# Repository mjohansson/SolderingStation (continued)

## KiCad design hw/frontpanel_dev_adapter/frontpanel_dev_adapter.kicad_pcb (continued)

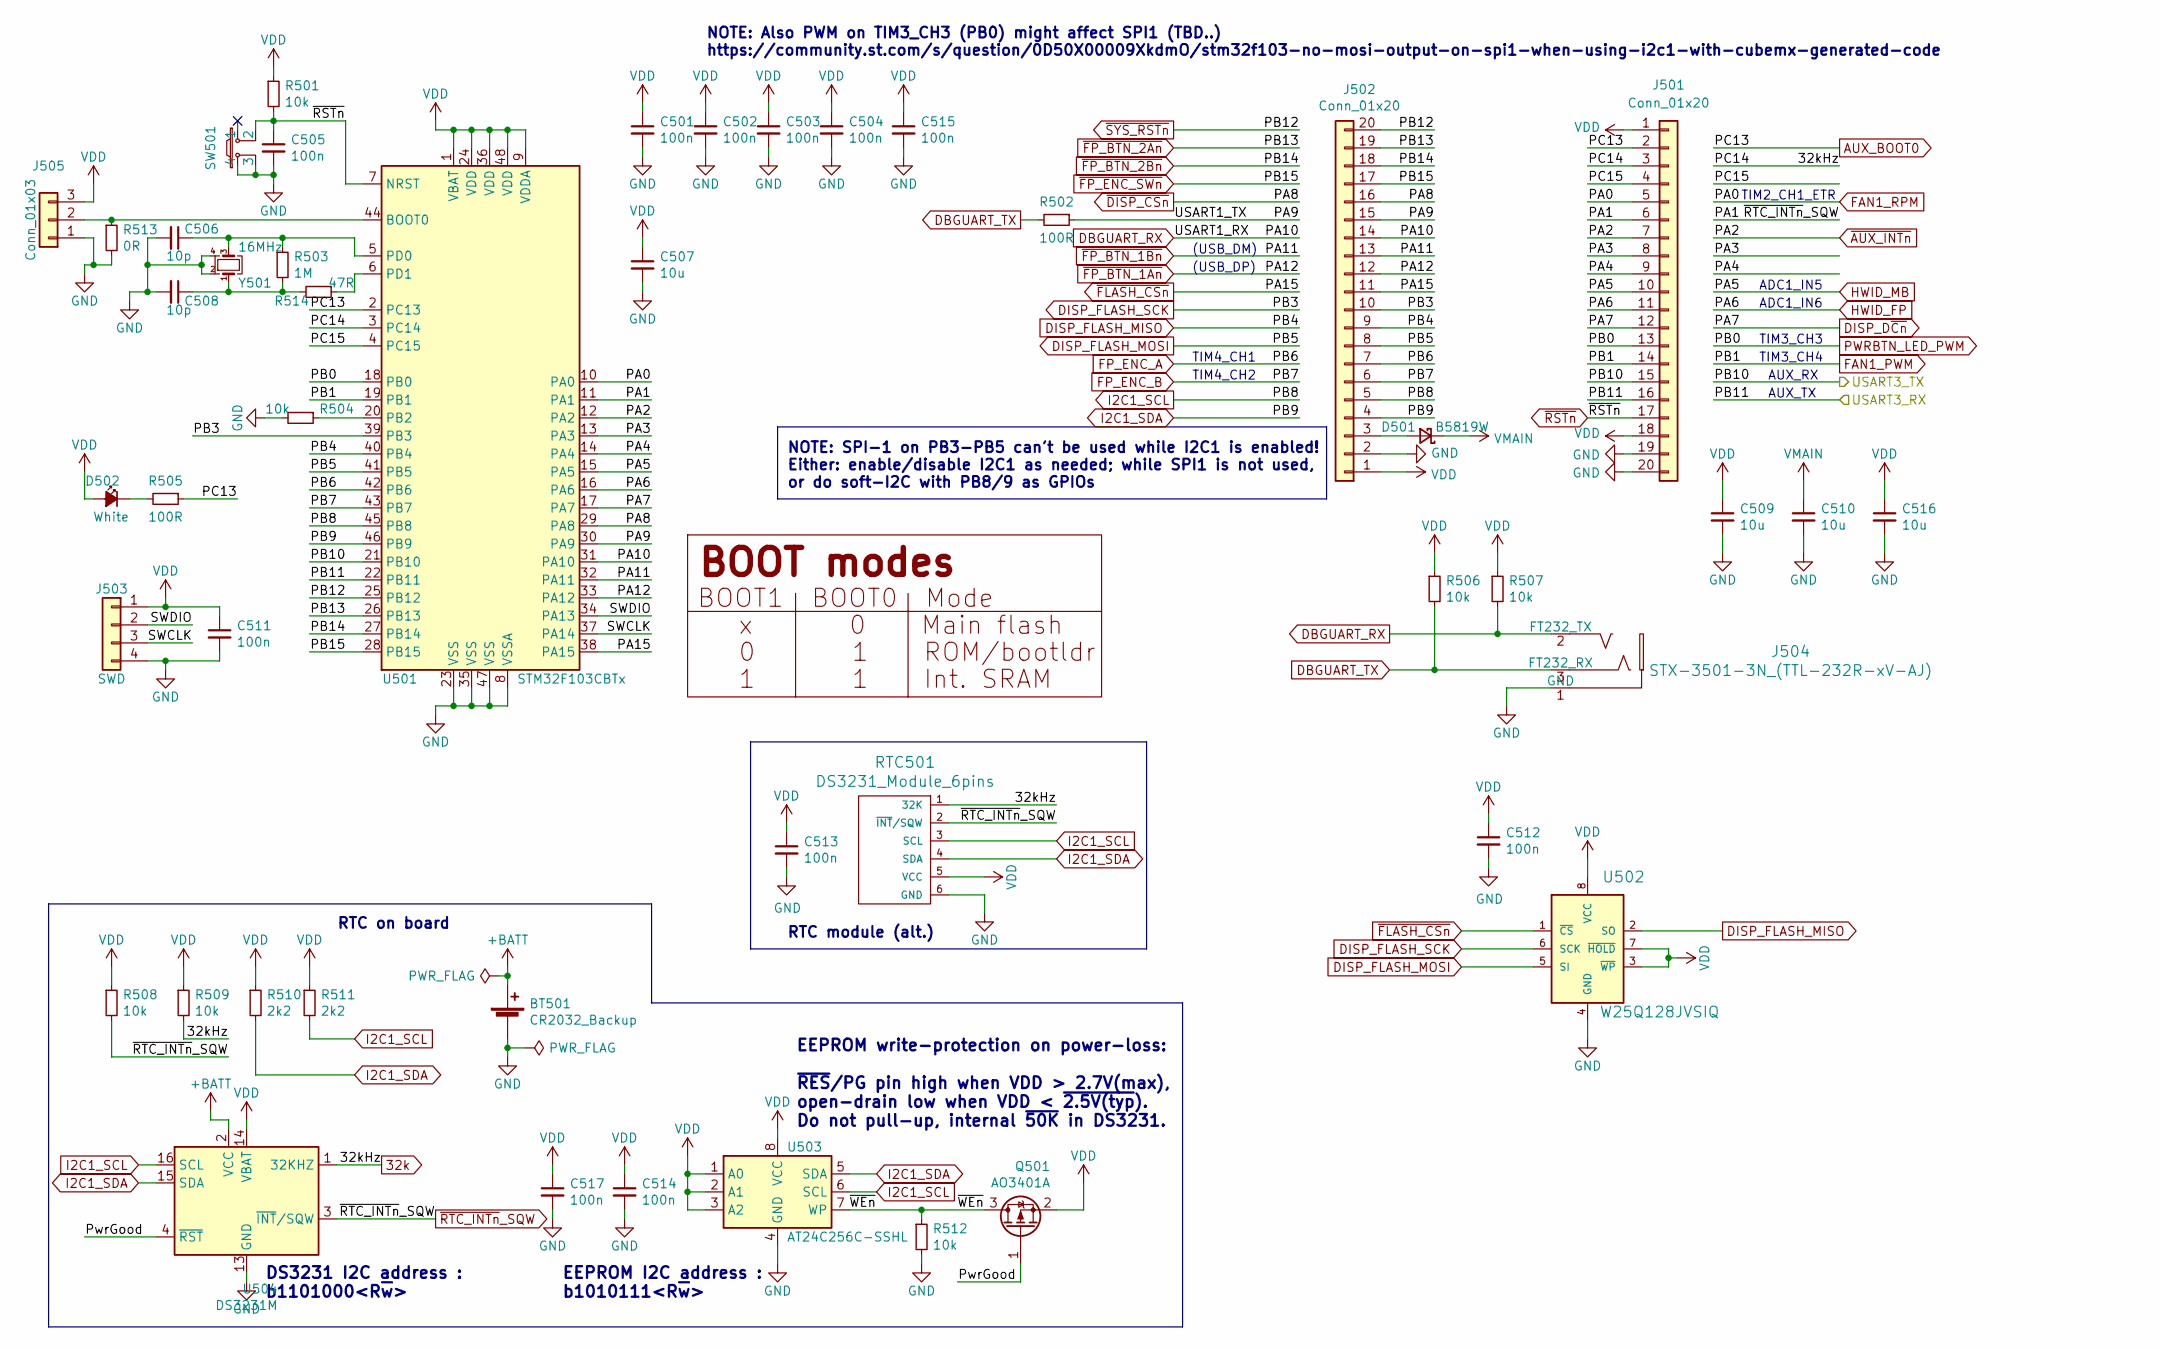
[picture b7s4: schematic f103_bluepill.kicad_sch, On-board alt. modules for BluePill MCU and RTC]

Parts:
BT501: CR2032_Backup; CR2032_coincell_holder
C501, C502, C503, C504, C505, C511, C512, C513, C514, C515, C517: 100n; C_0402_1005Metric; LCSC C1525
C506, C508: 10p; C_0402_1005Metric; LCSC C32949
C507, C509, C510, C516: 10u; C_0603_1608Metric; LCSC C19702
D501: B5819W; D_SOD-123; LCSC C8598
D502: White; LED_0603_1608Metric; LCSC C2290
J501, J502: Conn_01x20; PinSocket_1x20_P2.54mm_Vertical
J503: SWD; PinHeader_1x04_P2.54mm_Horizontal
J504: STX-3501-3N_(TTL-232R-xV-AJ); STX3501_smd
J505: Conn_01x03; PinHeader_1x03_P2.54mm_Vertical
Q501: AO3401A; SOT-23; LCSC C15127
R501, R504, R506, R508, R509, R512: 10k; R_0402_1005Metric; LCSC C25744
R502, R505: 100R; R_0402_1005Metric; LCSC C25076
R503: 1M; R_0402_1005Metric; LCSC C26083
R507: 10k; R_0402_1005Metric
R510, R511: 2k2; R_0402_1005Metric; LCSC C25879
R513: 0R; R_0402_1005Metric; LCSC C17168
R514: 47R; R_0402_1005Metric; LCSC C25118
RTC501: DS3231_Module_6pins; DS3231_module_6pin_horizontal_mnt
SW501: SKHUxxE010; SKHU
U501: STM32F103CBTx; LQFP-48_7x7mm_P0.5mm; LCSC C8304
U502: W25Q128JVSIQ; SOIC-8_5.23x5.23mm_P1.27mm; LCSC C97521
U503: AT24C256C-SSHL; SO-8_3.9x4.9mm_P1.27mm; LCSC C6482
U504: DS3231M; SOIC-16W_7.5x10.3mm_P1.27mm; LCSC C37663
Y501: 16MHz; Crystal_SMD_3225-4Pin_3.2x2.5mm; LCSC C13738

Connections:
32k: J501.3, R509.2, RTC501.1 (32K), U501.3 (PC14), U504.1 (32KHZ); also elsewhere on the board
+BATT: BT501.1 (+), U504.2 (VCC)
/F429Discovery connection/AUXUART7_RX: J501.16, U501.22 (PB11); also elsewhere on the board
/MCU / Bluepill/PA3: J501.8, U501.13 (PA3)
/MCU / Bluepill/PA4: J501.9, U501.14 (PA4)
/MCU / Bluepill/PA9: J502.15, R502.1, U501.30 (PA9)
/MCU / Bluepill/PC15: J501.4, U501.4 (PC15)
/MCU / Bluepill/PwrGood: Q501.1 (G), U504.4 (~RST)
/MCU / Bluepill/SWCLK: J503.3, U501.37 (PA14)
/MCU / Bluepill/SWDIO: J503.2, U501.34 (PA13)
/MCU / Bluepill/USART3_TX: J501.15, U501.21 (PB10); also elsewhere on the board
/MCU / Bluepill/~WEn~: Q501.3 (D), R512.1, U503.7 (WP)
AUX_BOOT0: J501.2, R505.1, U501.2 (PC13); also elsewhere on the board
DBGUART_RX: J502.14, J504.2 (FT232_TX), R507.2, U501.31 (PA10); also elsewhere on the board
DBGUART_TX: J504.3 (FT232_RX), R502.2, R506.2; also elsewhere on the board
DISP_D~Cn~: J501.12, U501.17 (PA7); also elsewhere on the board
DISP_FLASH_MISO: J502.9, U501.40 (PB4), U502.2 (SO); also elsewhere on the board
DISP_FLASH_MOSI: J502.8, U501.41 (PB5), U502.5 (SI); also elsewhere on the board
DISP_FLASH_SCK: J502.10, U501.39 (PB3), U502.6 (SCK); also elsewhere on the board
FAN1_PWM: J501.14, U501.19 (PB1); also elsewhere on the board
FAN1_RPM: J501.5, U501.10 (PA0); also elsewhere on the board
FP_ENC_A: J502.7, U501.42 (PB6); also elsewhere on the board
FP_ENC_B: J502.6, U501.43 (PB7); also elsewhere on the board
HWID_FP: J501.11, U501.16 (PA6); also elsewhere on the board
HWID_MB: J501.10, U501.15 (PA5); also elsewhere on the board
I2C1_SCL: J502.5, R511.2, RTC501.3 (SCL), U501.45 (PB8), U503.6 (SCL), U504.16 (SCL); also elsewhere on the board
I2C1_SDA: J502.4, R510.2, RTC501.4 (SDA), U501.46 (PB9), U503.5 (SDA), U504.15 (SDA); also elsewhere on the board
unnamed: C506.1, R503.1, U501.5 (PD0), Y501.3
unnamed: C508.1, R503.2, R514.2, Y501.1
unnamed: D501.2 (A), J502.3
unnamed: D502.1 (K), R505.2
unnamed: J505.2, R513.1, U501.44 (BOOT0)
unnamed: R504.1, U501.20 (PB2)
unnamed: R514.1, U501.6 (PD1)
PWRBTN_LED_PWM: J501.13, U501.18 (PB0); also elsewhere on the board
VDD: C501.1, C502.1, C503.1, C504.1, C507.1, C509.1, C511.1, C512.1, C513.1, C514.1, C515.1, C516.1, C517.1, D502.2 (A), J501.1, J501.18, J502.1, J503.1, J505.3, Q501.2 (S), R501.1, R506.1, R507.1, R508.1, R509.1, R510.1, R511.1, RTC501.5 (VCC), U501.1 (VBAT), U501.9 (VDDA), U501.24 (VDD), U501.36 (VDD), U501.48 (VDD), U502.3 (~WP), U502.7 (~HOLD), U502.8 (VCC), U503.1 (A0), U503.2 (A1), U503.3 (A2), U503.8 (VCC), U504.14 (VBAT); also elsewhere on the board
VMAIN: C510.1, D501.1 (K); also elsewhere on the board
~AUX_INTn~: J501.7, U501.12 (PA2); also elsewhere on the board
~DISP_CSn~: J502.16, U501.29 (PA8); also elsewhere on the board
~FLASH_CSn~: J502.11, U501.38 (PA15), U502.1 (~CS); also elsewhere on the board
~FP_BTN_1An~: J502.12, U501.33 (PA12); also elsewhere on the board
~FP_BTN_1Bn~: J502.13, U501.32 (PA11); also elsewhere on the board
~FP_BTN_2An~: J502.19, U501.26 (PB13); also elsewhere on the board
~FP_BTN_2Bn~: J502.18, U501.27 (PB14); also elsewhere on the board
~FP_ENC_SWn~: J502.17, U501.28 (PB15); also elsewhere on the board
~RSTn~: C505.1, J501.17, R501.2, SW501.2, U501.7 (NRST); also elsewhere on the board
~RTC_INTn~_SQW: J501.6, R508.2, RTC501.2 (~INT/SQW), U501.11 (PA1), U504.3 (~INT/SQW); also elsewhere on the board
~SYS_RSTn~: J502.20, U501.25 (PB12); also elsewhere on the board

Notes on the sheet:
(USB_DM)
DS3231 I2C address : b1101000<R~{w}>
TIM4_CH2
NOTE: Also PWM on TIM3_CH3 (PB0) might affect SPI1 (TBD..) https://community.st.com/s/question/0D50X00009XkdmO/stm32f103-no-mosi-output-on-spi1-when-using-i2c1-with-cubemx-generated-code
TIM3_CH4
AUX_TX
AUX_RX
TIM3_CH3
EEPROM write-protection on power-loss: ~{RES}/PG pin high when VDD > 2.7V(max), open-drain low when VDD < ~{2.5V(typ}). Do not pull-up, internal ~{50K} in DS3231.
ADC1_IN5
NOTE: SPI-1 on PB3-PB5 can't be used while I2C1 is enabled! Either: enable/disable I2C1 as needed; while SPI1 is not used, or do soft-I2C with PB8/9 as GPIOs
TIM2_CH1_ETR
(USB_DP)
EEPROM I2C address : b1010111<R~{w}>
ADC1_IN6
RTC on board
TIM4_CH1
RTC module (alt.)

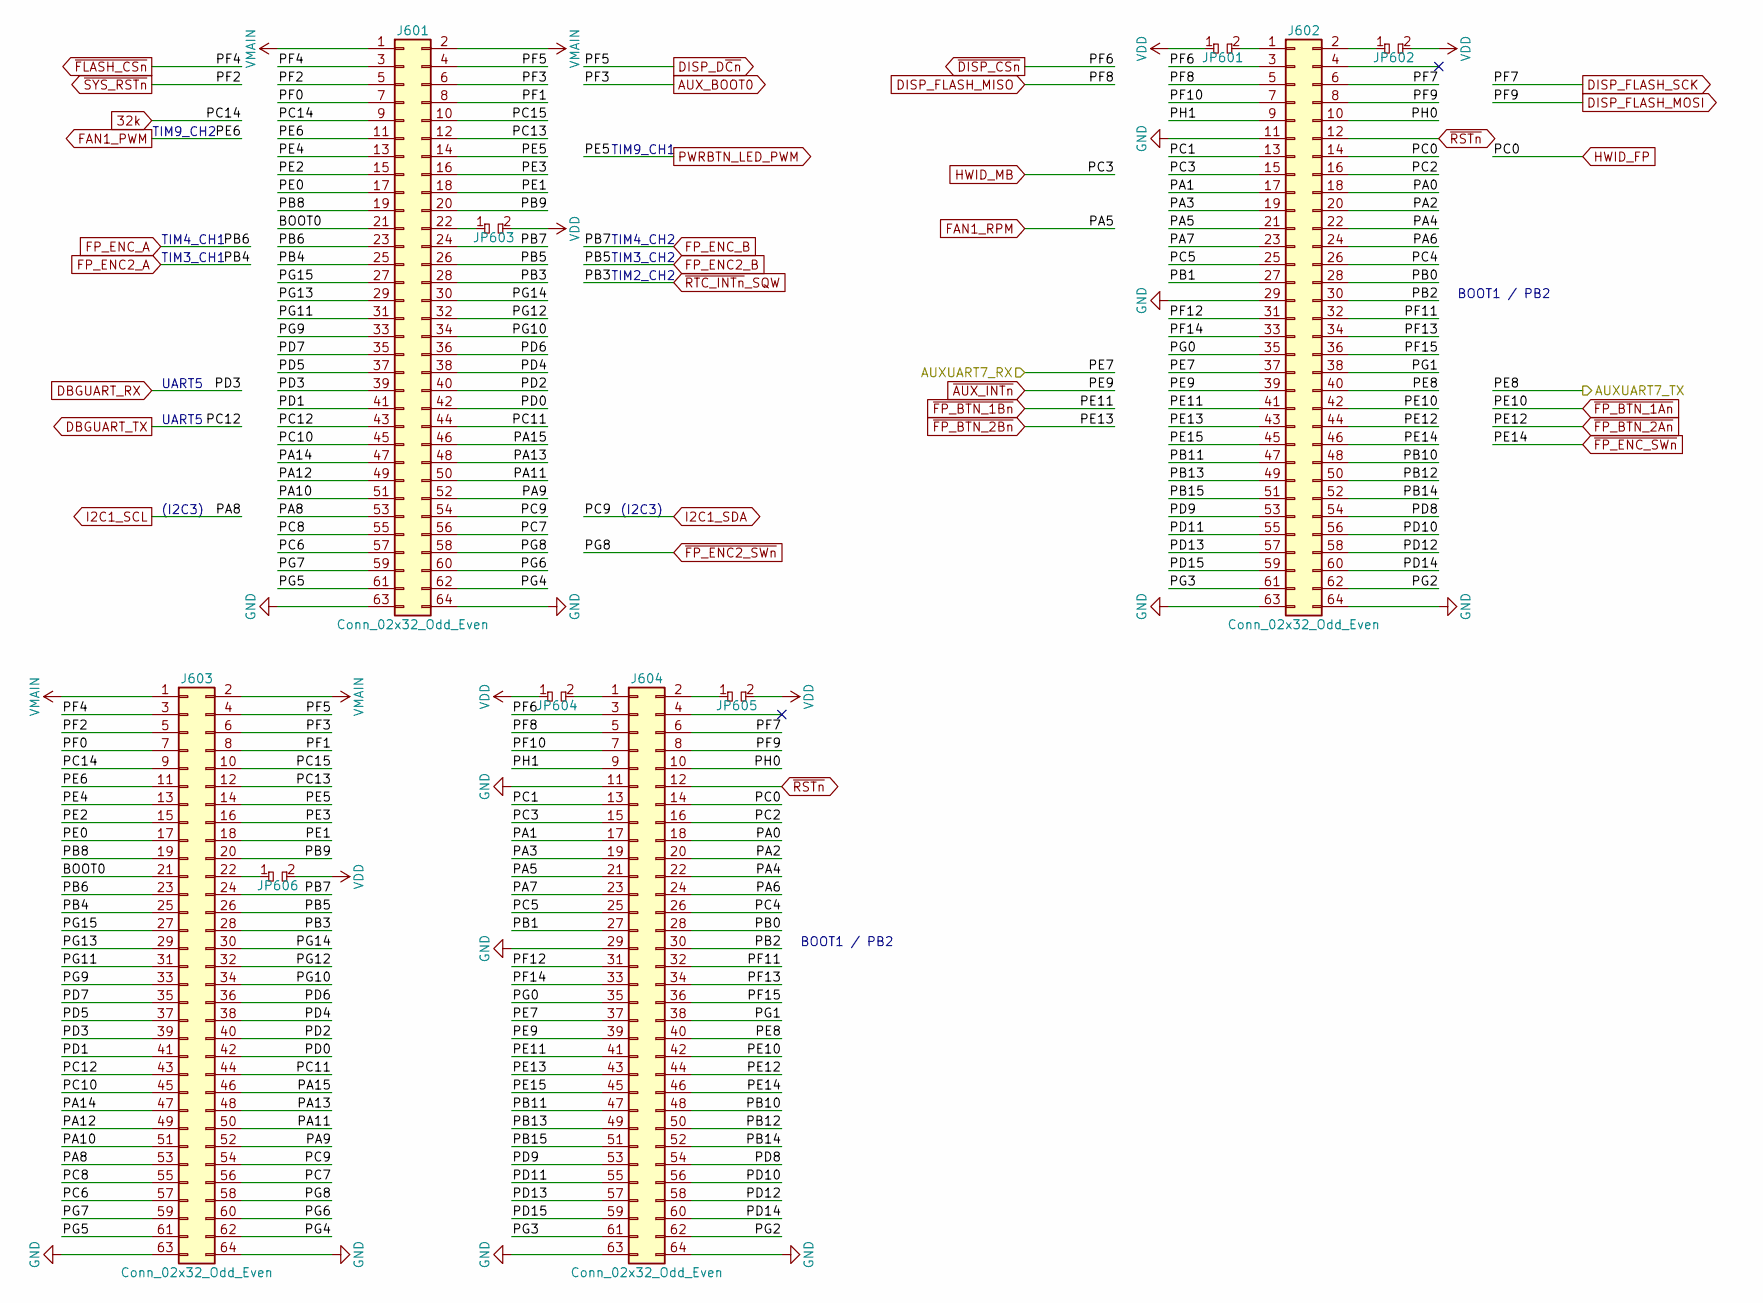
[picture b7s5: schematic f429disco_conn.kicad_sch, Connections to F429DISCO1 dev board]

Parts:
J601, J602: Conn_02x32_Odd_Even; PinSocket_2x32_P2.54mm_Vertical
J603, J604: Conn_02x32_Odd_Even; PinHeader_2x32_P2.54mm_Vertical
JP601, JP602, JP603, JP604, JP605, JP606: dogbone_2_ud; db2_ud_0402

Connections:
32k: J601.9, J603.9; also elsewhere on the board
/F429Discovery connection/AUXUART7_RX: J602.37, J604.37; also elsewhere on the board
/F429Discovery connection/AUXUART7_TX: J602.40, J604.40; also elsewhere on the board
/F429Discovery connection/BOOT0: J601.21, J603.21
/F429Discovery connection/PA0: J602.18, J604.18
/F429Discovery connection/PA1: J602.17, J604.17
/F429Discovery connection/PA2: J602.20, J604.20
/F429Discovery connection/PA3: J602.19, J604.19
/F429Discovery connection/PA4: J602.22, J604.22
/F429Discovery connection/PA6: J602.24, J604.24
/F429Discovery connection/PA7: J602.23, J604.23
/F429Discovery connection/PA9: J601.52, J603.52
/F429Discovery connection/PA10: J601.51, J603.51
/F429Discovery connection/PA11: J601.50, J603.50
/F429Discovery connection/PA12: J601.49, J603.49
/F429Discovery connection/PA13: J601.48, J603.48
/F429Discovery connection/PA14: J601.47, J603.47
/F429Discovery connection/PA15: J601.46, J603.46
/F429Discovery connection/PB0: J602.28, J604.28
/F429Discovery connection/PB1: J602.27, J604.27
/F429Discovery connection/PB2: J602.30, J604.30
/F429Discovery connection/PB8: J601.19, J603.19
/F429Discovery connection/PB9: J601.20, J603.20
/F429Discovery connection/PB10: J602.48, J604.48
/F429Discovery connection/PB11: J602.47, J604.47
/F429Discovery connection/PB12: J602.50, J604.50
/F429Discovery connection/PB13: J602.49, J604.49
/F429Discovery connection/PB14: J602.52, J604.52
/F429Discovery connection/PB15: J602.51, J604.51
/F429Discovery connection/PC1: J602.13, J604.13
/F429Discovery connection/PC2: J602.16, J604.16
/F429Discovery connection/PC4: J602.26, J604.26
/F429Discovery connection/PC5: J602.25, J604.25
/F429Discovery connection/PC6: J601.57, J603.57
/F429Discovery connection/PC7: J601.56, J603.56
/F429Discovery connection/PC8: J601.55, J603.55
/F429Discovery connection/PC10: J601.45, J603.45
/F429Discovery connection/PC11: J601.44, J603.44
/F429Discovery connection/PC13: J601.12, J603.12
/F429Discovery connection/PC15: J601.10, J603.10
/F429Discovery connection/PD0: J601.42, J603.42
/F429Discovery connection/PD1: J601.41, J603.41
/F429Discovery connection/PD2: J601.40, J603.40
/F429Discovery connection/PD4: J601.38, J603.38
/F429Discovery connection/PD5: J601.37, J603.37
/F429Discovery connection/PD6: J601.36, J603.36
/F429Discovery connection/PD7: J601.35, J603.35
/F429Discovery connection/PD8: J602.54, J604.54
/F429Discovery connection/PD9: J602.53, J604.53
/F429Discovery connection/PD10: J602.56, J604.56
/F429Discovery connection/PD11: J602.55, J604.55
/F429Discovery connection/PD12: J602.58, J604.58
/F429Discovery connection/PD13: J602.57, J604.57
/F429Discovery connection/PD14: J602.60, J604.60
/F429Discovery connection/PD15: J602.59, J604.59
/F429Discovery connection/PE0: J601.17, J603.17
/F429Discovery connection/PE1: J601.18, J603.18
/F429Discovery connection/PE2: J601.15, J603.15
/F429Discovery connection/PE3: J601.16, J603.16
/F429Discovery connection/PE4: J601.13, J603.13
/F429Discovery connection/PE15: J602.45, J604.45
/F429Discovery connection/PF0: J601.7, J603.7
/F429Discovery connection/PF1: J601.8, J603.8
/F429Discovery connection/PF10: J602.7, J604.7
/F429Discovery connection/PF11: J602.32, J604.32
/F429Discovery connection/PF12: J602.31, J604.31
/F429Discovery connection/PF13: J602.34, J604.34
/F429Discovery connection/PF14: J602.33, J604.33
/F429Discovery connection/PF15: J602.36, J604.36
/F429Discovery connection/PG0: J602.35, J604.35
/F429Discovery connection/PG1: J602.38, J604.38
/F429Discovery connection/PG2: J602.62, J604.62
/F429Discovery connection/PG3: J602.61, J604.61
/F429Discovery connection/PG4: J601.62, J603.62
/F429Discovery connection/PG5: J601.61, J603.61
/F429Discovery connection/PG6: J601.60, J603.60
/F429Discovery connection/PG7: J601.59, J603.59
/F429Discovery connection/PG9: J601.33, J603.33
/F429Discovery connection/PG10: J601.34, J603.34
/F429Discovery connection/PG11: J601.31, J603.31
/F429Discovery connection/PG12: J601.32, J603.32
/F429Discovery connection/PG13: J601.29, J603.29
/F429Discovery connection/PG14: J601.30, J603.30
/F429Discovery connection/PG15: J601.27, J603.27
/F429Discovery connection/PH0: J602.10, J604.10
/F429Discovery connection/PH1: J602.9, J604.9
AUX_BOOT0: J601.6, J603.6; also elsewhere on the board
DBGUART_RX: J601.39, J603.39; also elsewhere on the board
DBGUART_TX: J601.43, J603.43; also elsewhere on the board
DISP_D~Cn~: J601.4, J603.4; also elsewhere on the board
DISP_FLASH_MISO: J602.5, J604.5; also elsewhere on the board
DISP_FLASH_MOSI: J602.8, J604.8; also elsewhere on the board
DISP_FLASH_SCK: J602.6, J604.6; also elsewhere on the board
FAN1_PWM: J601.11, J603.11; also elsewhere on the board
FAN1_RPM: J602.21, J604.21; also elsewhere on the board
FP_ENC2_A: J601.25, J603.25; also elsewhere on the board
FP_ENC2_B: J601.26, J603.26; also elsewhere on the board
FP_ENC_A: J601.23, J603.23; also elsewhere on the board
FP_ENC_B: J601.24, J603.24; also elsewhere on the board
HWID_FP: J602.14, J604.14; also elsewhere on the board
HWID_MB: J602.15, J604.15; also elsewhere on the board
I2C1_SCL: J601.53, J603.53; also elsewhere on the board
I2C1_SDA: J601.54, J603.54; also elsewhere on the board
unnamed: J601.22, JP603.1
unnamed: J602.1, JP601.2
unnamed: J602.2, JP602.1
unnamed: J603.22, JP606.1
unnamed: J604.1, JP604.2
unnamed: J604.2, JP605.1
PWRBTN_LED_PWM: J601.14, J603.14; also elsewhere on the board
VDD: JP601.1, JP602.2, JP603.2, JP604.1, JP605.2, JP606.2; also elsewhere on the board
VMAIN: J601.1, J601.2, J603.1, J603.2; also elsewhere on the board
~AUX_INTn~: J602.39, J604.39; also elsewhere on the board
~DISP_CSn~: J602.3, J604.3; also elsewhere on the board
~FLASH_CSn~: J601.3, J603.3; also elsewhere on the board
~FP_BTN_1An~: J602.42, J604.42; also elsewhere on the board
~FP_BTN_1Bn~: J602.41, J604.41; also elsewhere on the board
~FP_BTN_2An~: J602.44, J604.44; also elsewhere on the board
~FP_BTN_2Bn~: J602.43, J604.43; also elsewhere on the board
~FP_ENC2_SWn~: J601.58, J603.58; also elsewhere on the board
~FP_ENC_SWn~: J602.46, J604.46; also elsewhere on the board
~RSTn~: J602.12, J604.12; also elsewhere on the board
~RTC_INTn~_SQW: J601.28, J603.28; also elsewhere on the board
~SYS_RSTn~: J601.5, J603.5; also elsewhere on the board

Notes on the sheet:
TIM4_CH2
TIM4_CH1
TIM3_CH1
TIM3_CH2
UART5
TIM9_CH1
BOOT1 / PB2
(I2C3)
TIM2_CH2
TIM9_CH2

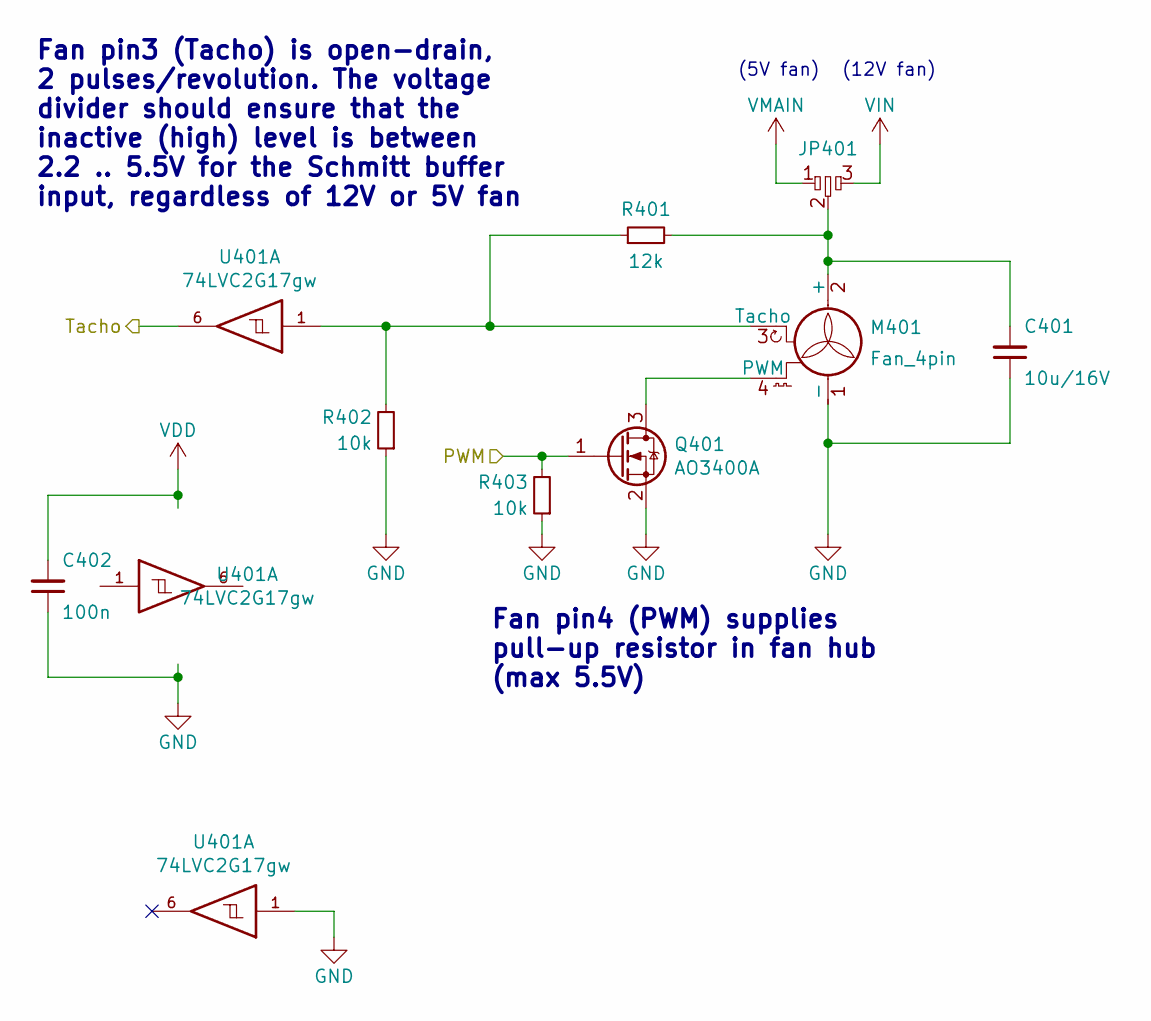
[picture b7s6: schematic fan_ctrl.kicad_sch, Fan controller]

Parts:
C401: 10u/16V; C_0805_2012Metric; LCSC C15850
C402: 100n; C_0402_1005Metric; LCSC C1525
JP401: dogbone_3_ud; db3_ud_0603
M401: Fan_4pin; FanPinHeader_1x04_P2.54mm_Vertical
Q401: AO3400A; SOT-23; LCSC C20917
R401: 12k; R_0402_1005Metric; LCSC C25752
R402, R403: 10k; R_0402_1005Metric; LCSC C25744
U401: 74LVC2G17gw; SOT-363_SC-70-6; LCSC (DNM) C80500

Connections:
FAN1_PWM: Q401.1 (G), R403.2; also elsewhere on the board
FAN1_RPM: U401.6; also elsewhere on the board
unnamed: C401.2, JP401.2, M401.2 (+), R401.2
unnamed: M401.4 (PWM), Q401.3 (D)
VDD: C402.2, U401.5 (VCC); also elsewhere on the board
VIN: JP401.3; also elsewhere on the board
VMAIN: JP401.1; also elsewhere on the board

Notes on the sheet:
Fan pin4 (PWM) supplies pull-up resistor in fan hub (max 5.5V)
(5V fan)
(12V fan)
Fan pin3 (Tacho) is open-drain, 2 pulses/revolution. The voltage divider should ensure that the inactive (high) level is between 2.2 .. 5.5V for the Schmitt buffer input, regardless of 12V or 5V fan

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
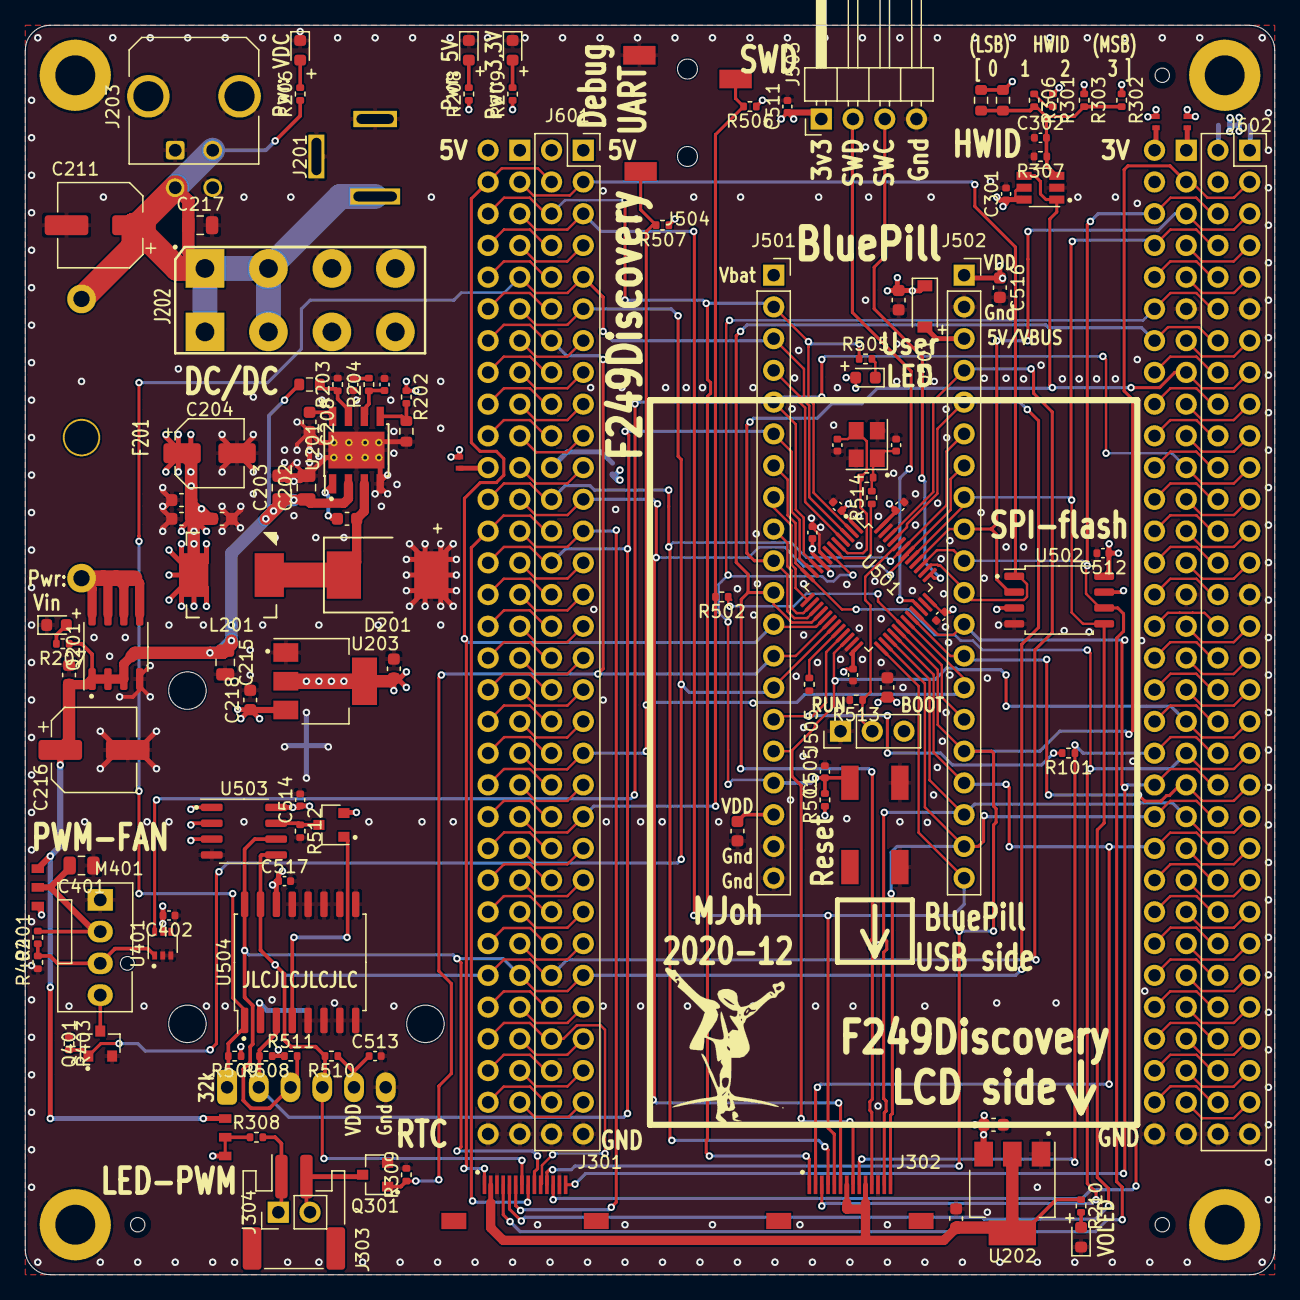
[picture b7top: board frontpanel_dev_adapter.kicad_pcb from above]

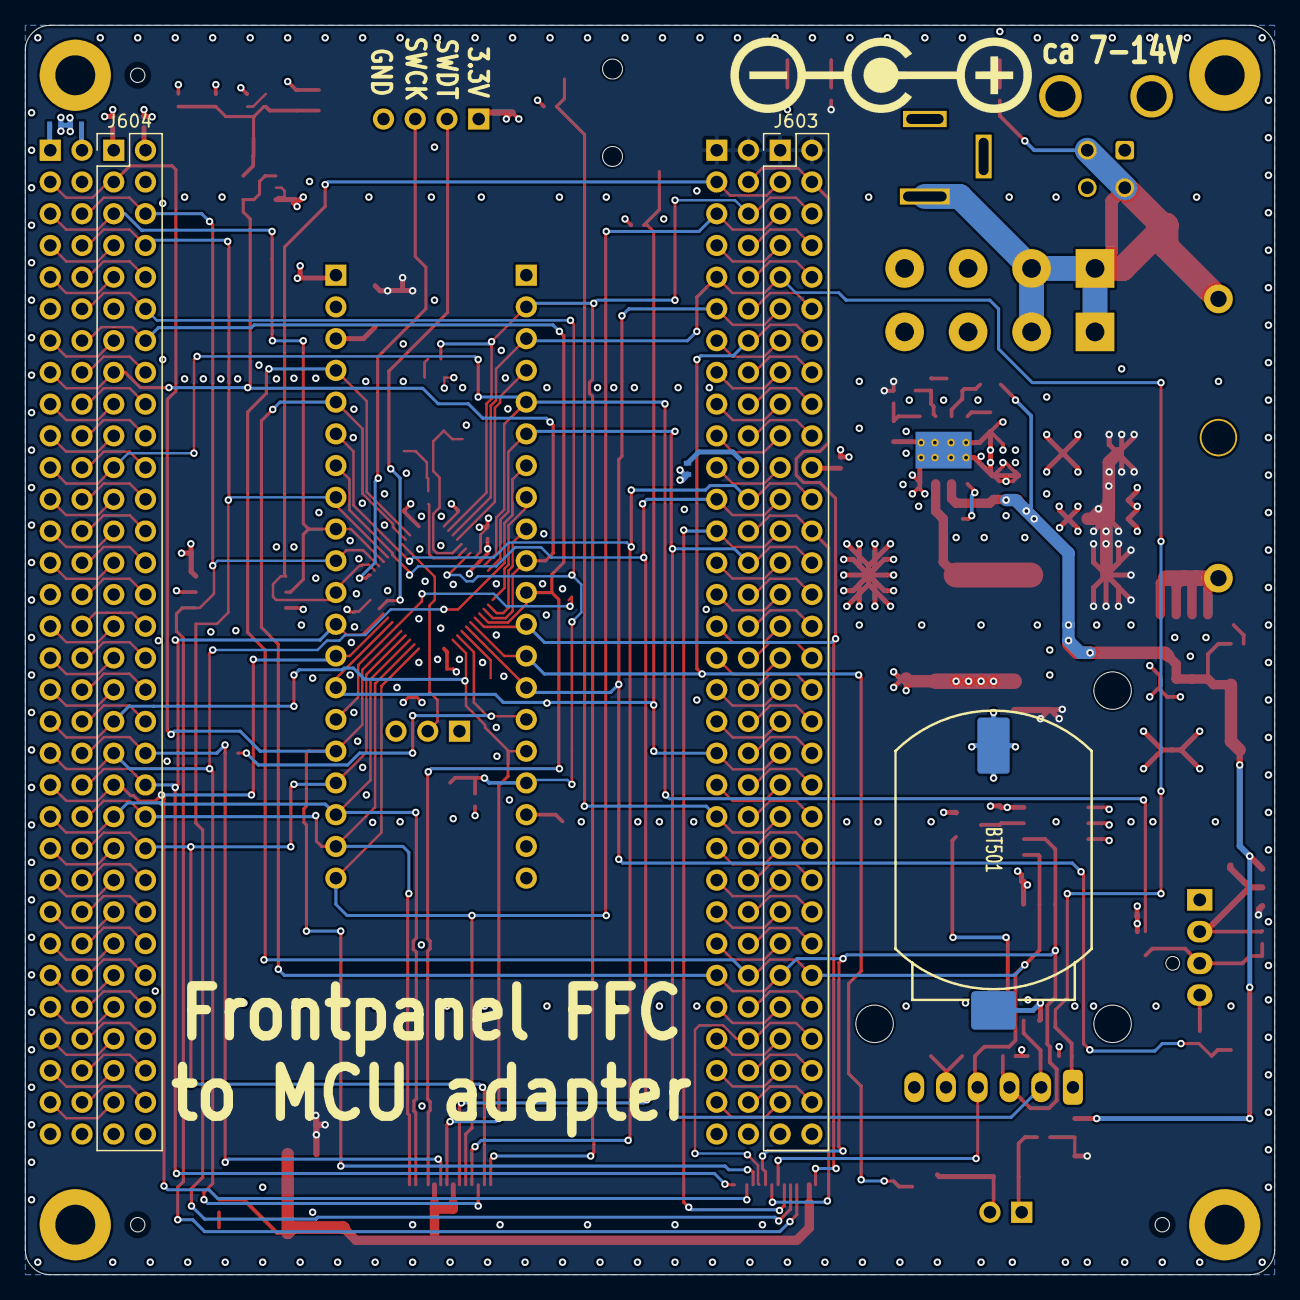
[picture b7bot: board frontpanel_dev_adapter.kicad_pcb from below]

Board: 4 copper layers, 100.0 x 100.0 mm, 137 parts (6 on the bottom side), 165 nets.

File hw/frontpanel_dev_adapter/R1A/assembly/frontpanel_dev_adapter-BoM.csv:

Comment,Designator,Footprint,LCSC Part Number
10u/16V,"C202,C203,C215,C217,C401",Capacitor_SMD:C_0805_2012Metric,C15850
10u/10V,"C205,C206,C207,C212,C218",Capacitor_SMD:C_0603_1608Metric,C19702
15n,C208,Capacitor_SMD:C_0603_1608Metric,C1596
10pF,C209,Capacitor_SMD:C_0402_1005Metric,C32949
3n3,C210,Capacitor_SMD:C_0402_1005Metric,C26404
100n,"C201,C214",Capacitor_SMD:C_0603_1608Metric,C14663
10u,"C213,C219,C507,C509,C510,C516",Capacitor_SMD:C_0603_1608Metric,C19702
100n,"C301,C302,C402,C501,C502,C503,C504,C505,C511,C512,C513,C514,C515,C517",Capacitor_SMD:C_0402_1005Metric,C1525
10p,"C506,C508",Capacitor_SMD:C_0402_1005Metric,C32949
MBRS340T3G,D201,customlib_mj_fp:MBRS3xx_SMC_CASE_403AC,C40326
Yellow,"D202,D203",LED_SMD:LED_0603_1608Metric,C72038
Green,"D204,D205,D206",LED_SMD:LED_0603_1608Metric,C72043
B5819W,D501,Diode_SMD:D_SOD-123,C8598
White,D502,LED_SMD:LED_0603_1608Metric,C2290
AO4407A,Q201,customlib_mj_fp:SOIC-8_3.9x4.9mm_P1.27mm,C16072
AO3400A,"Q301,Q401",Package_TO_SOT_SMD:SOT-23,C20917
AO3401A,Q501,Package_TO_SOT_SMD:SOT-23,C15127
100R,"R101,R502,R505",Resistor_SMD:R_0402_1005Metric,C25076
390k,R201,Resistor_SMD:R_0603_1608Metric,C23150
68k,R203,Resistor_SMD:R_0402_1005Metric,C36871
10k,"R202,R204,R206,R207,R302,R309,R402,R403,R501,R504,R506,R507,R508,R509,R512",Resistor_SMD:R_0402_1005Metric,C25744
1k8,R205,Resistor_SMD:R_0603_1608Metric,C4177
2k2,"R208,R510,R511",Resistor_SMD:R_0402_1005Metric,C25879
1k,"R209,R210",Resistor_SMD:R_0402_1005Metric,C11702
20k,"R301,R303,R306",Resistor_SMD:R_0402_1005Metric,C25765
160k,"R304,R305",Resistor_SMD:R_0603_1608Metric,C22813
27k,R307,Resistor_SMD:R_0402_1005Metric,C25771
0R,"R308,R513",Resistor_SMD:R_0402_1005Metric,C17168
12k,R401,Resistor_SMD:R_0402_1005Metric,C25752
1M,R503,Resistor_SMD:R_0402_1005Metric,C26083
47R,R514,Resistor_SMD:R_0402_1005Metric,C25118
TPS54332DDA,U201,Package_SO:TI_SO-PowerPAD-8_ThermalVias,C41312
TLV1117LV30DCY,"U202,U203",Package_TO_SOT_SMD:SOT-223-3_TabPin2,C15578
STM32F103CBTx,U501,Package_QFP:LQFP-48_7x7mm_P0.5mm,C8304
W25Q128JVSIQ,U502,Package_SO:SOIC-8_5.23x5.23mm_P1.27mm,C97521
AT24C256C-SSHL,U503,Package_SO:SO-8_3.9x4.9mm_P1.27mm,C6482
DS3231M,U504,Package_SO:SOIC-16W_7.5x10.3mm_P1.27mm,C37663
16MHz,Y501,Crystal:Crystal_SMD_3225-4Pin_3.2x2.5mm,C13738

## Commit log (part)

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2020-04-30 Initial commit. Mostly docs & appnotes and generic project tree structure
2020-04-30 Project logo (medium size)
2020-04-30 Add also empty dirs
2020-05-05 Added ds for Si4735 (why not?)
2020-05-05 Added STM32 appnote (oscillator design guide)
2020-05-05 Added generic 6x6mm tactile pushbutton. This variant found (cheap) on LCSC
2020-05-05 MJ solderstn_mb schematic : mcu_1 & ethernet
2020-05-05 remove obsolete local/temp libs from project lib-tables
2020-05-09 Bunch of docs renamed; some new (e.g. crystals); new 3d-models e.g. RS_Pro power-button; minor updates to eth, stm32 schematics
2020-08-18 Summer vacation 2020 updates: * Front panel design rev 1 complete (incl Experimental outer board with optional linear touch sensors) * MB schematics AlmostDone(tm) - 'old' pinout supporting only one 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
2020-08-18 Lots of mech-stuff (could use a good clean-up eventually)
2020-08-18 Alternative CubeMX pin-out to enable dual rotary encoders,,,
2020-08-18 Reverse-voltage protection PFET
2020-08-19 (pdf schematics from yesterday and after today's new pinout)
2020-08-19 * Remove separate REED_PULLUP_EN pin; instead bias the Reedswitches with the per-channel KTY bias (buffered Vref) * Add separate mini cut-out sub-PCB for 3.5 headphone connector at back-panel (must b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
2020-08-19 * pinheader/socket for headphone sub-PCB 2x3 -> 2x5 (greater mechanical stability) * printed WIP-schematics pdf for 08-19
2020-08-21 Some more docs (Molex connectors & schmitt-trigger buffers)
2020-08-21 Daily schematics updates (pdf) 20-08-20
2020-08-21 Created PCB outline 160.5x220, with 3mm keepout lines (in silk) along the sides (This is abs.max size of board; cut off and cut-out as needed...)
2020-08-22 Updated display-board sch & PCB with optional left-hand rotary encoder instead of pwrbtn. Printed MB schematic updates PDF for 20-08-21
2020-08-22 Mech: test-assembly of 2nd rotary on display-board. Tight fit, but a teeny-tiny bit of grinding the rotary will fix it :)
2020-08-22 gitignore: FreeCad-backup files & zip-files etc
2020-08-22 Updated FP display board with changes to hybrid 2nd rotary holder. Updated & more stuff to the mech asm-testing of inner-plate/2nd rotary
2020-08-23 Started on 1.6mm FR4 back-panel
2020-08-23 mech: small pocket under pwrbtn holder compensating for HASL bumps on the 5 new pins for 2nd enc
2020-08-23 Corrected several ERC issues. Re-annotated & assigned all footprints except 32k xtal (will prob. replace with RTC module anyway)
2020-08-24 Pinout changes to add DS3231 RTC module instead of 32kHz LSE xtal (still keep SMD pads as placeholders). Minor ERC fixes. All footprints specified
2020-08-24 Printed MB schematics pdf for 08-23 updates
2020-08-24 mech updates (3d-holders and assemblies)
2020-08-24 Updated display-board with mech updates. Default version is original left PwrBtn + right Rotary
2020-08-24 Minor updates to MB and box asmtesting
2020-08-24 Updated mech-models of display-board & outer-panel with StepUp. (Had to plot silk-layers as dxf from Kicad to allow StepUp to import them)
2020-08-24 Added updated 'real' display-board and outer front-panel to main 3d test-assmbly, freash from StepUp conversion. Added 28mm rotary Al-button as alternative to the old
2020-08-26 Backpanel: Initial placement of Schaffner AC-inlet, Schurter secondary fuse-holder and 2x Weller DIN7
2020-08-26 Trimmed MB pcb outline to 160.0 mm width
2020-08-30 Updated STL of left 3dholder
2020-08-31 Added back-panel cutouts for Wurth RJ45 (LAN) and TE's USB-A & USB-B connectors
2020-08-31 Updated back-panel with 3.5mm audio jack & Dsub-9 cut-outs
2020-09-03 Tentative placement of speakers on MB, CUI 70x31mm and 20x30mm, resepectively
2020-09-03 Created simple volume model of CES-503528 (however obv. too big to fit)
2020-09-05 Created rudimentary volume modell of CUI CES-30207 mini speaker
2020-09-05 Updated 3d asm-testing with exported MB w. speakers. Issue: 70mm speakers collide with Meanwell, -1mm in Z. Have to add washers to 5mm spacers
2020-09-05 Updated speaker-assembly to avoid collisions; no-margins might-fit, requires washers and coutersunk screws. This is fine! :)
2020-10-06 Updated USB-A conn to CUI UJ2-AH-1-SMT because retention pads are SMD. Also better USB-A cutout in back panel. Updated 3d test model
2020-10-06 New component: 4mm banana socket - Stäubli LB-I4R-A (23.0190-21)
2020-10-06 Added 4mm banana earth connector to back panel. Moved DIN-connectors slightly to fit. Updated 3d test model
2020-10-07 Add 12V DC-out (Molex Nano-Fit 1x02) and SMA in back-panel, for FM antenna & ext. ant.amp. Updated Dsub9 conn to correct component & placement on MB.
2020-10-07 New components : Molex NanoFit 1x02 docs
2020-10-24 *) Add some docs (JST PH spk conn., SPI-flash, Molex NanoFit 12V backpanel conn.) *) MB cutouts for front-panel features *) Change PwrBtn LED conn. Molex MicroClasp -> JST PH2 to avoid througholes + 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
2020-10-26 3d-printed template for making MW & fan drill holed in Hammond bottom plate
2020-10-26 About to shuffle stuff around on MB; save old placements as a backup board file (also mech asm-testing)
2020-10-26 Backpanel: slightly move fuseholder & PE banana conn
2020-10-27 mech: testing alternate placement of Meanwell PSU; centered-fwd.
    + : more space in back for PSU cabling etc
    + : space on both sides to fit 80mm internal speakers (tilted sideways, beneath MB PCB)
    + : no interference at Power-button
    - : no space for any chassis fans (maybe cram one in sideways, but why..?)
2020-10-27 backpanel: minor position adjustments
2020-10-28 New mech main-track selected: "centered PSU" + "Mirrored back panel". Minor cleanups & re-alignments.
    (Yet ToDo: all MB adjustments...)
2020-10-29 Updated MB cutouts, placements to new PSU-centered & 'mirrored' rearpanel layout. Schaffner FN283 (AC-inlet) now defaults to placed at inside rearpanel position -> rear looks (a bit) less cluttered
2020-10-30 New component : Schurter OGN 0031.82x1 PCB fuse-holder
2020-10-30 Rearpanel: IDC 2x5 instead of Dsub9 as dbg/bootstrp conn. Remove secondary fuseholder; rearrange DIN, P.E. banana, dbg. for more space. MainBoard: Rotate MW PSU 180deg (optimize for 230V through PwrB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
2020-10-31 Update bottom-plate with drill-holes for new PSU placement. Interior M3 3mm holes for original orientaion; diagonal M3s for rotated orientation
2020-10-31 Added (plenty of) vent slots to bottom plate
2020-11-03 docs for new components - Wurth WR-FAST quick-connect cable-conn. blades
2020-11-03 Clean-up - remove unused/old files
2020-11-04 MB: *) add LED on DC-in pwr-rail *) fix misnamed audio signals
2020-11-05 MB: 1) remove 2x fan ctrls 2) MCU pin-out for a VS1063 3) add VS1063 DSP/codec to audio path (WIP)
2020-11-09 Docs & DS for TS5A3159A mux, VS1063a, ESD diodes etc
2020-11-13 MB: sch) minor fixups (some added decoupling, some missing connections); brd) some initial placements
2020-11-15 Add doc about modding the Amphenol DIN-7 connector to be Weller compatible
2020-11-15 MB: some more (tentative) placement
2020-11-19 Rename doc-RTC dir. Add some RTC- & eeprom doc
2020-11-22 New sub-sheet for RTC; added on-board alternatives to ready-made DS3231-module
2020-11-22 Copy of JLCs parts library
2020-11-23 New sub-project : DS3231M RTC-module w. JLCPCB components
2020-11-24 Quick 1st layout & route of the RTC sub-module
2020-11-24 Quick & dirty 2x4 panel of the RTC module, for v-scoring (ToDo: sanity-check DRC with JLC rules)
2020-12-01 New breakout-board: 87DC-201 'speed-buttons' bridges (if JLC complains about break-away variant in the frontpanel PCB)
2020-12-01 Bridge board: add placeholder JLC serial label in silk
2020-12-07 Some placement (audio, RTC)
2020-12-07 (just updated caches)
2020-12-17 Create CubeMX projects for FFC Adapter board (one for F103, one for F429-disco)
2020-12-17 Preliminary sch & early PCB setup for an FFC adapter board design
2020-12-21 Frontpanel adapter: PCB placement done incl logo, mounting holes. Some silk notations."
2020-12-23 FP adapter/devboard: some initial routing
2020-12-30 FP adapter/dev board: add datasheet for DC/DC inductor and diode
2020-12-30 FP adapter/dev board: *routing DONE* ; minor pinout tweaks (optimize routing); fix some missing 3d models
2020-12-31 FP adapter board: Added LCSC partnumbers to all components to be PnP:ed; Finalized some silk additions; Generated Gerbers, BoM & pnp-files for JCL assembly
2020-12-31 Backpanel: added fill zones & labels/icons in silk-screen on back
2020-12-31 Backpanel: Change labels/icons to solder-mask cutout variants instead (for e.g. ENIG on black)
2020-12-31 Backpanel : Generated alernative gerbers for soldermask labels/icons
2020-12-31 Backpanel (solder-mask labels) : Remove Cu-fill on inside. Keep all-board fill on outside for now (KISS)
2020-12-31 Frontpanel-outer : minor tweaks to align some traces with MCU pads; generated Gerbers
2020-12-31 Frontpanel-inner : generated gerbers
2021-01-03 Update frontpanel-inner-plate: Remove breakaway subboards; slight improve routing and plane fills. R2A files generated but not ordered
2021-01-03 Adjust separate bridge-board panel for potential production (R1A *not* ordered though)
2021-01-09 MB : some uncommitted changes, dont remember what
2021-01-09 New sub-board : JLink/STlink -> SolderStation debug adapter (WIP)
2021-01-10 rename step-file
2021-01-13 MB: major update of footprints, LCSC part numbers and Basic/Extended library indicator, for _most_ of the BoM. (Also removed JP1101/JP1102, bypass jmprs)
2021-01-13 Commit backpanel gfx/labels/icons pngs
2021-01-13 MB: update xtal osc load caps from 27pF -> 10pF
2022-01-12 fw/f439C/alt_ss2k_cube project : Cube F429 lib update
2022-01-12 Fw/f429 : some default usart/utils; wip
2022-01-12 Some more doc files
2022-01-12 solderstn_mb : Misc uncommitted changes I dont remember...
2022-01-12 Basic glcd convert-tool for the 4bpp OLED
2022-01-15 Kicad 6.0 : Most of SS2k & subprojects updated to kicad6 The projects should from now on be opened through the .kicad_pro files instead of .pro, etc. NOTE: Kicad 6 is now used. Kicad5 is NOT able to 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
2022-01-18 docs : stm32f103 + 12V secondary fuses
2022-01-20 solderstation_mb: some file cleanup
    * dxf's, step's and FreeCad prj-files moved to new subdir ./3d_exports/
    * add missing file
    * remove some v5 cruft
2022-01-20 ss_backpanel-mirrored : files cleanup, added ./3d_exports/
2022-01-21 Mechanical mockup of the rear 95mm of mainboard (unrouted)
    A 2L, 95x160mm mockup connector- and footprint test board was cut down from full size MB.
    (In hindsight, should probably just have ordered the full board outline!)
    * 5pcs ordered from JLCPCB for mechnical sanity-testing
2022-01-21 Frontpanel_dev_adapter : kicad 5 -> kicad 6
2022-01-21 doc/stm32f429 : docs & appnoted added (incl F429Discovery devboard files)
2022-01-21 docs : some examples & ref-info for VS1053-1063
2022-02-02 Placeholder 3d-models for rear-panel (w. conns), PSU, Bottom-plate, front-panel (w. conns), outer fp
    With these placeholder mech. objects, the build-in 3d view of MB pcb features most of the mechanical
    objects that constrain components placements. So 3d-view can be used to quickly check and iterate
    placements to avoid 3d collisions, without having to first export MB STEP into FreeCAD and muck around
    only to have to repeat again for each iteration
2022-02-26 F103 FP_DEV: bitbanged SW-I2C, TMP100 drv, DWT util fns
2022-02-26 docs: I2C std.
2022-04-07 solderstn_mb::power - changed generic 2x2 connector to customlib_mj:Molex_MicroFit 2x2
    (and a whole bunch of other automatic changes, crap)
2024-02-26 hw: long-standing uncommitted stuff; mostly auto-updates (v7) fw: remove L052 tree (CMSIS & std-HAL shouldn't be committed and it was the wrong device name anyway)
2024-02-26 (renamed doc/STM32L052... to doc/STM32L053...)
